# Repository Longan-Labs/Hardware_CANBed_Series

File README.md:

Eagle file sor [CANBed Series](https://www.longan-labs.cc/can-bus/canbed.html)

Include:

* [CANBed V1](https://www.longan-labs.cc/1030008.html)
* [CANBed FD](https://www.longan-labs.cc/1030009.html)
* [CANBed M0](https://www.longan-labs.cc/1030014.html)
* [CANBed M4](https://www.longan-labs.cc/1030013.html)

Click on [Longan-Labs.cc](https://www.longan-labs.cc/) to get the product you need.

Contact [support@longan-labs.cc](support@longan-labs.cc) if you need help.

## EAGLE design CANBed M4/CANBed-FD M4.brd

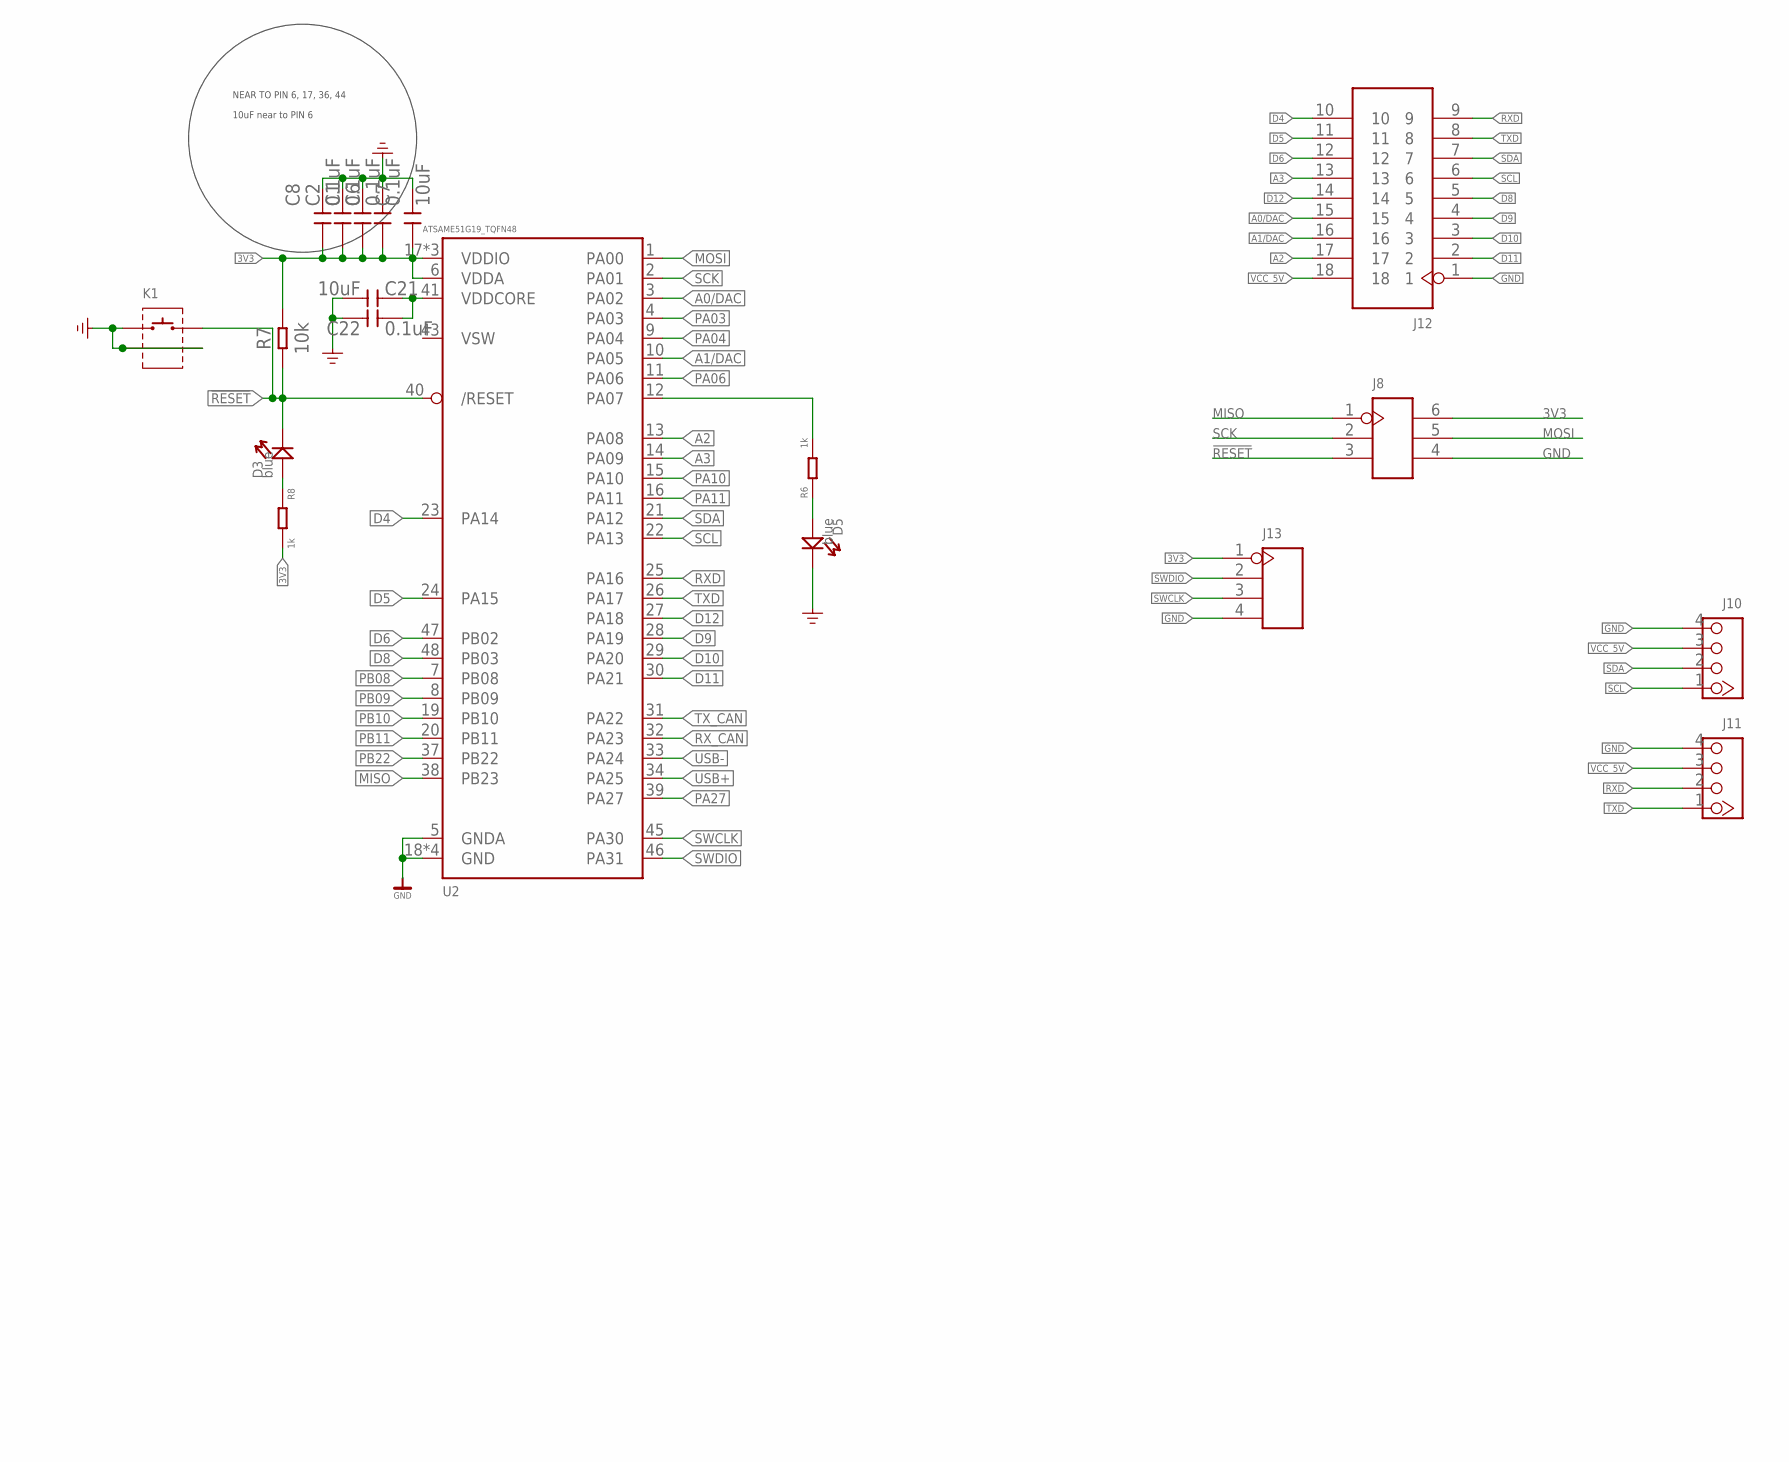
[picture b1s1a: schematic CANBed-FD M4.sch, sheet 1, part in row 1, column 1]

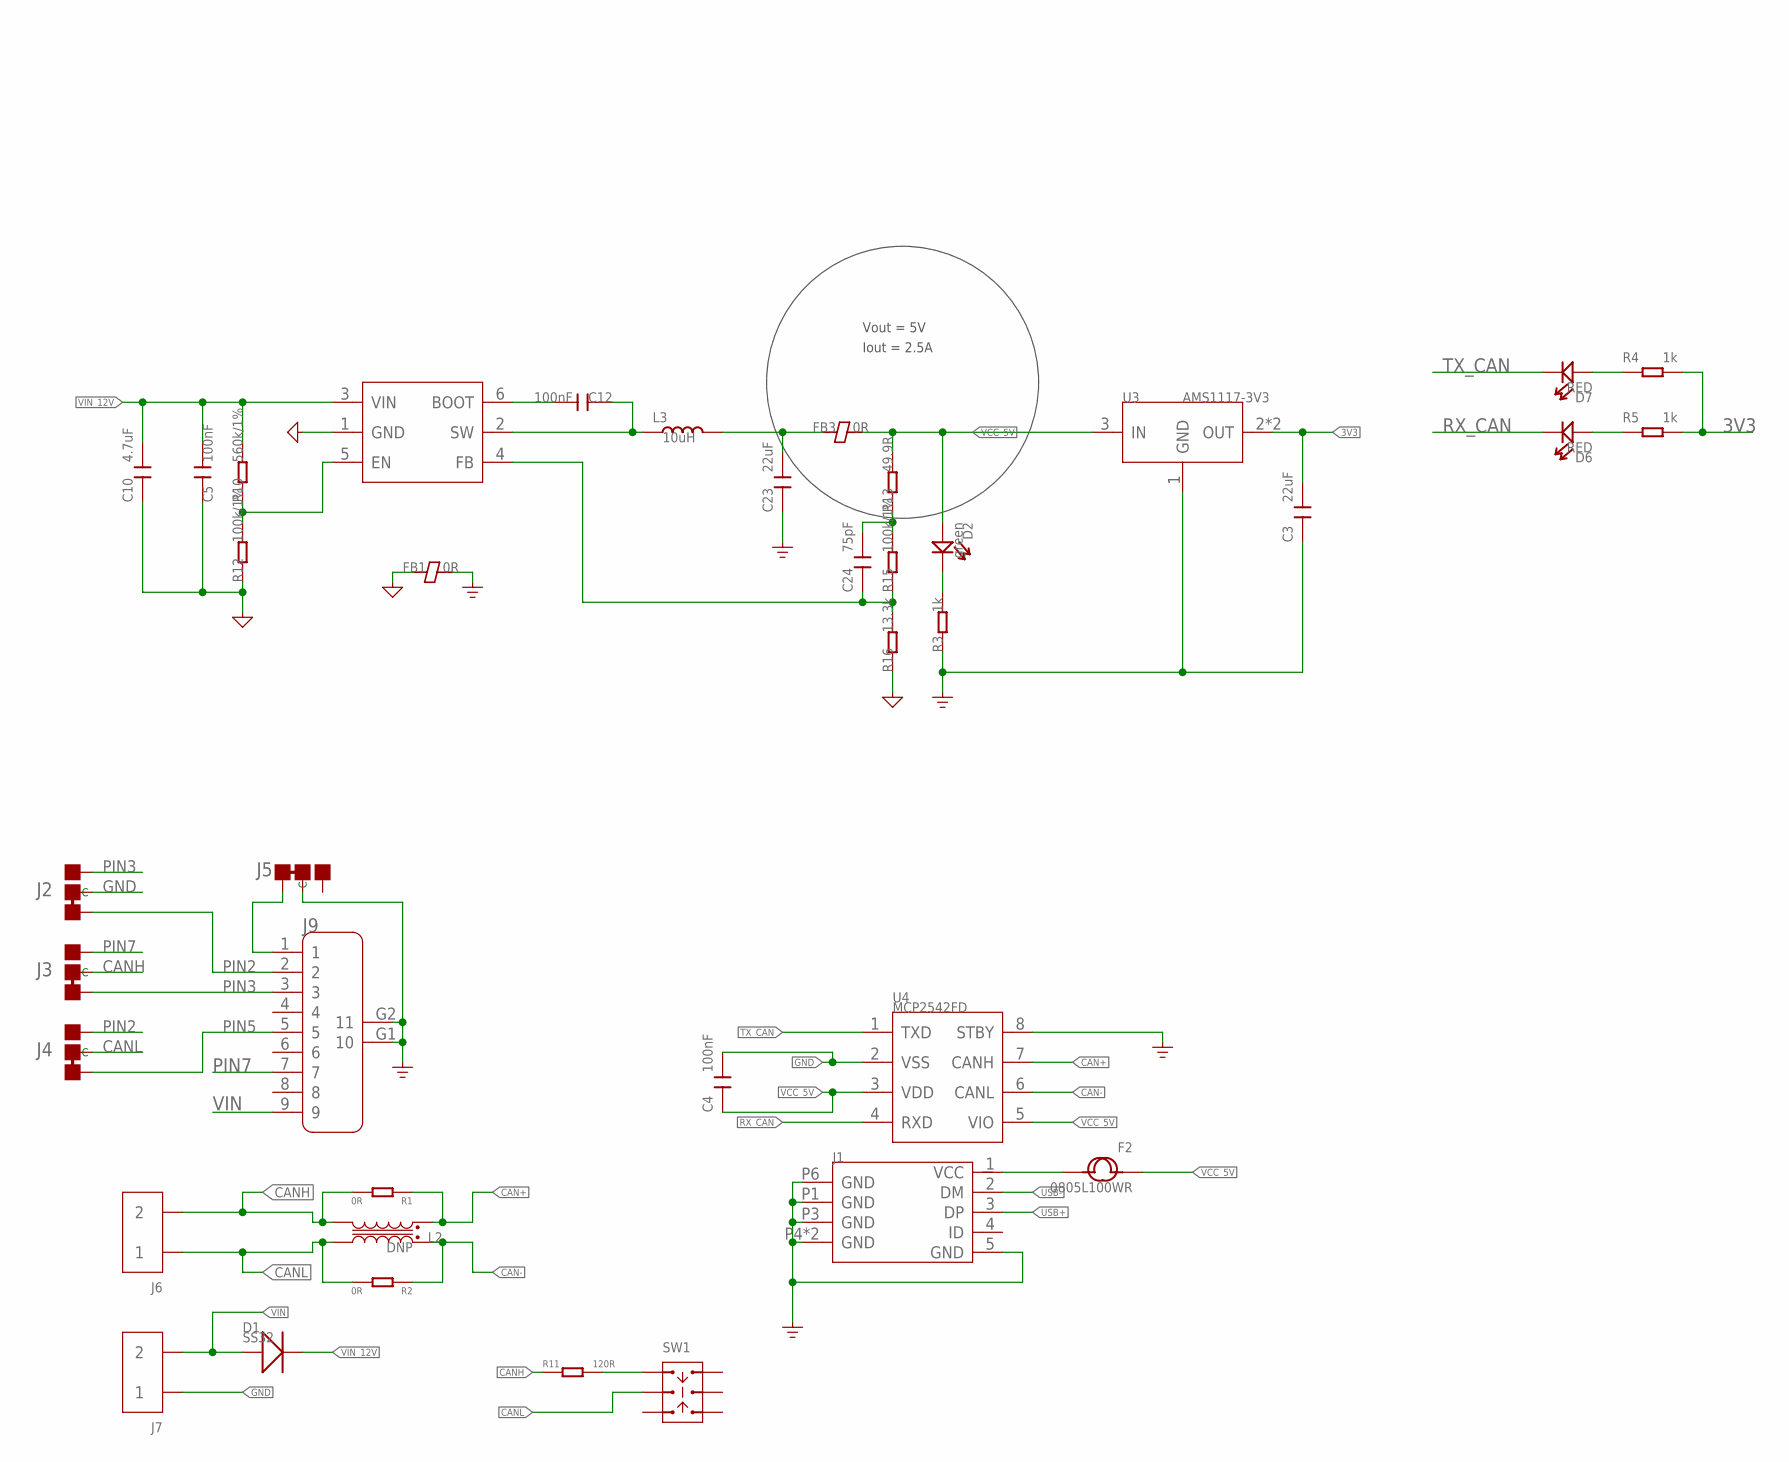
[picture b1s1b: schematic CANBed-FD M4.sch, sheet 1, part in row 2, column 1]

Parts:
C1, C2, C6, C8, C21: 0.1uF; C0603
C3, C23: 22uF; C1206
C4, C5, C12: 100nF; C0603
C7, C22: 10uF; C0603
C10: 4.7uF; C1206
C24: 75pF; C0603
D1: SS32; DO-214AC
D2: green; LED-0603
D3, D5: blue; LED-0603
D6, D7: RED; LED-0603
F2: 0805L100WR; F0805
FB1, FB3: 0R; F0805
J1: MICRO-USB5+4P-320010050; MICRO-USB5+5P-SMD-0.65-7.2X5.06MM
J2, J3, J4, J5: JUMPER-3P-SHORT; 3P-SMD-SHORT
J6, J7: SCREW-TERMINAL-2P'5.08'; H2-5.0-10.5X8.0MM
J8: HEADER-2X3P-2.54; H2X3-2.54
J9: DB9'MEAL'; DB9-MEAL
J10, J11: 320110033; HW4-2.0
J12: HEADER-2X9P-2.54; H2X9-2.54
J13: HEADER-4P-65/35MIL; H4-2.54
K1: BUTTON-2+2P; SW2+2P-7.7X2.75X3.95MM
L2: DNP; INT4-0.85-2X1.25X1.2MM
L3: 10uH; INT2-SMD-6.6X7.1X3MM
R1, R2: 0R; R0603
R3, R4, R5, R6, R8: 1k; R0603
R7: 10k; R0603
R10: 560k/1%; R0603
R11: 120R; R0603
R12, R15: 100k/1%; R0603
R13: 49.9R; R0603
R16: 13.3k; R0603
SW1: SWITCH-2CH-6P-311010004; SW6-2.54-9.0X3.5X3.2+2.0MM
U1: PMIC-TPS54302; SOT-23-6
U2: ATSAME51G19_TQFN48; TQFN48_7MM; MPN ATSAME51G19A-MF
U3: AMS1117-3V3; SOT-223
U4: MCP2542FD; SOIC8-1.27-5X4MM

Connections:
3V3: C1.1, C2.1, C3.2, C6.1, C7.1, C8.1, J8.6, J13.1, R4.2, R5.2, R7.2, R8.2, U2.6 (VDDA), U2.17 (VDDIO), U2.36 (VDDIO), U2.44 (VDDIO), U3.2 (OUT), U3.TER (OUT)
!RESET: D3.-, J8.3, K1.2, R7.1, U2.40 (/RESET)
A0/DAC: J12.15, U2.3 (PA02)
A1/DAC: J12.16, U2.10 (PA05)
A2: J12.17, U2.13 (PA08)
A3: J12.13, U2.14 (PA09)
AGND: C5.1, C10.1, FB1.1, R12.1, R16.1, U1.1 (GND)
CAN+: L2.4, R1.1, U4.7 (CANH)
CAN-: L2.1, R2.1, U4.6 (CANL)
CANH: J3.MM (C), J6.2, L2.3, R1.2, R11.1
CANL: J4.MM (C), J6.1, L2.2, R2.2, SW1.COM1
D4: J12.10, U2.23 (PA14)
D5: J12.11, U2.24 (PA15)
D6: J12.12, U2.47 (PB02)
D8: J12.5, U2.48 (PB03)
D9: J12.4, U2.28 (PA19)
D10: J12.3, U2.29 (PA20)
D11: J12.2, U2.30 (PA21)
D12: J12.14, U2.27 (PA18)
EXT_PWR: F2.2, J1.1 (VCC)
GND: C1.2, C2.2, C3.1, C4.2, C6.2, C7.2, C8.2, C21.1, C22.2, C23.1, D5.-, FB1.2, J1.5 (GND), J1.P1 (GND), J1.P3 (GND), J1.P4 (GND), J1.P5 (GND), J1.P6 (GND), J2.MM (C), J5.MM (C), J7.1, J8.4, J9.G1 (10), J9.G2 (11), J10.4, J11.4, J12.1, J13.4, K1.1, K1.S1, K1.S2, R3.1, U2.5 (GNDA), U2.18 (GND), U2.35 (GND), U2.42 (GND), U2.THERMAL (GND), U3.1 (GND), U4.2 (VSS), U4.8 (STBY)
MISO: J8.1, U2.38 (PB23)
MOSI: J8.5, U2.1 (PA00)
unnamed: D3.+, R8.1
unnamed: D7.+, R4.1
unnamed: D2.-, R3.2
unnamed: R10.1, R12.2, U1.5 (EN)
unnamed: C21.2, C22.1, U2.41 (VDDCORE)
unnamed: R6.2, U2.12 (PA07)
unnamed: D5.+, R6.1
unnamed: C12.1, L3.1, U1.2 (SW)
unnamed: J5.11 (L), J9.1
unnamed: C12.2, U1.6 (BOOT)
unnamed: D6.+, R5.1
unnamed: R11.2, SW1.CH1A
unnamed: C23.2, FB3.1, L3.2
unnamed: C24.2, R13.1, R15.2
unnamed: C24.1, R15.1, R16.2, U1.4 (FB)
PA03: U2.4 (PA03)
PA04: U2.9 (PA04)
PA06: U2.11 (PA06)
PA10: U2.15 (PA10)
PA11: U2.16 (PA11)
PA27: U2.39 (PA27)
PB08: U2.7 (PB08)
PB09: U2.8 (PB09)
PB10: U2.19 (PB10)
PB11: U2.20 (PB11)
PB22: U2.37 (PB22)
PIN2: J2.11 (L), J4.00 (R), J9.2
PIN3: J2.00 (R), J3.11 (L), J9.3
PIN5: J4.11 (L), J9.5
PIN7: J3.00 (R), J9.7
RXD: J11.2, J12.9, U2.25 (PA16)
RX_CAN: D6.-, U2.32 (PA23), U4.4 (RXD)
SCK: J8.2, U2.2 (PA01)
SCL: J10.1, J12.6, U2.22 (PA13)
SDA: J10.2, J12.7, U2.21 (PA12)
SWCLK: J13.3, U2.45 (PA30)
SWDIO: J13.2, U2.46 (PA31)
TXD: J11.1, J12.8, U2.26 (PA17)
TX_CAN: D7.-, U2.31 (PA22), U4.1 (TXD)
USB+: J1.3 (DP), U2.34 (PA25)
USB-: J1.2 (DM), U2.33 (PA24)
VCC_5V: C4.1, D2.+, F2.1, FB3.2, J10.3, J11.3, J12.18, R13.2, U3.3 (IN), U4.3 (VDD), U4.5 (VIO)
VIN: D1.1 (+), J7.2, J9.9
VIN_12V: C5.2, C10.2, D1.2 (-), R10.2, U1.3 (VIN)

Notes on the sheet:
Vout = 5V
Iout = 2.5A
NEAR TO PIN 6, 17, 36, 44
10uF near to PIN 6

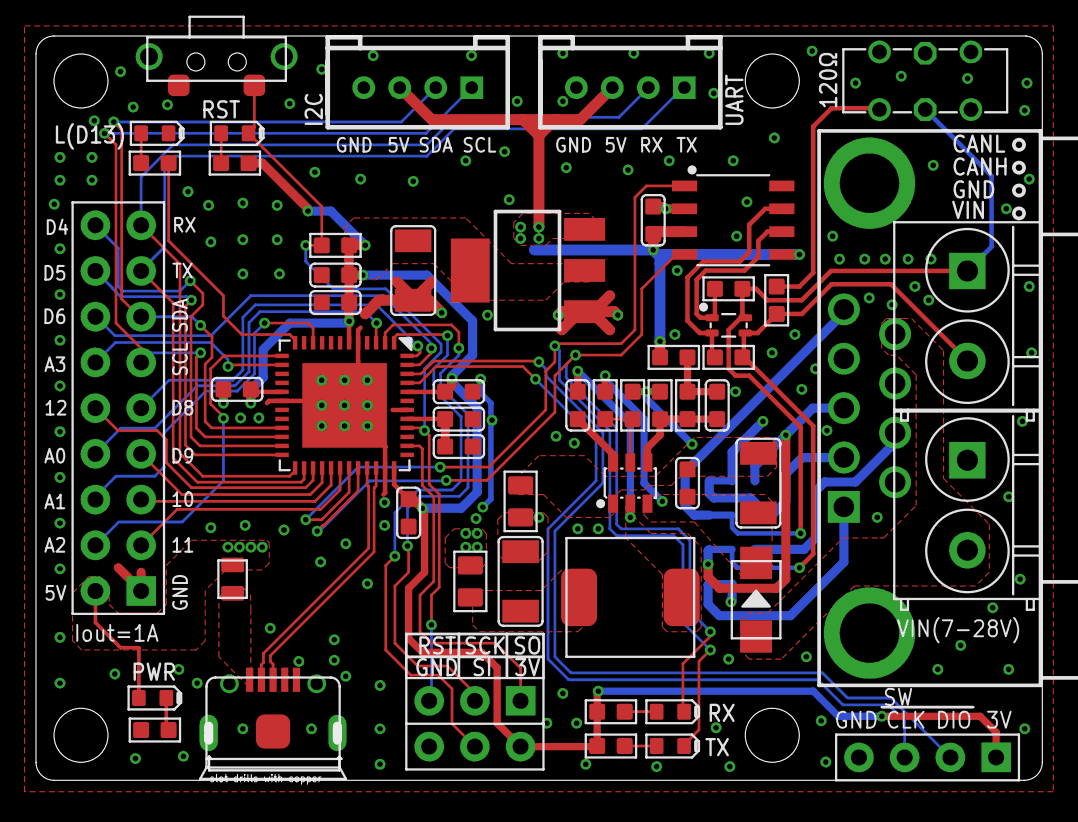
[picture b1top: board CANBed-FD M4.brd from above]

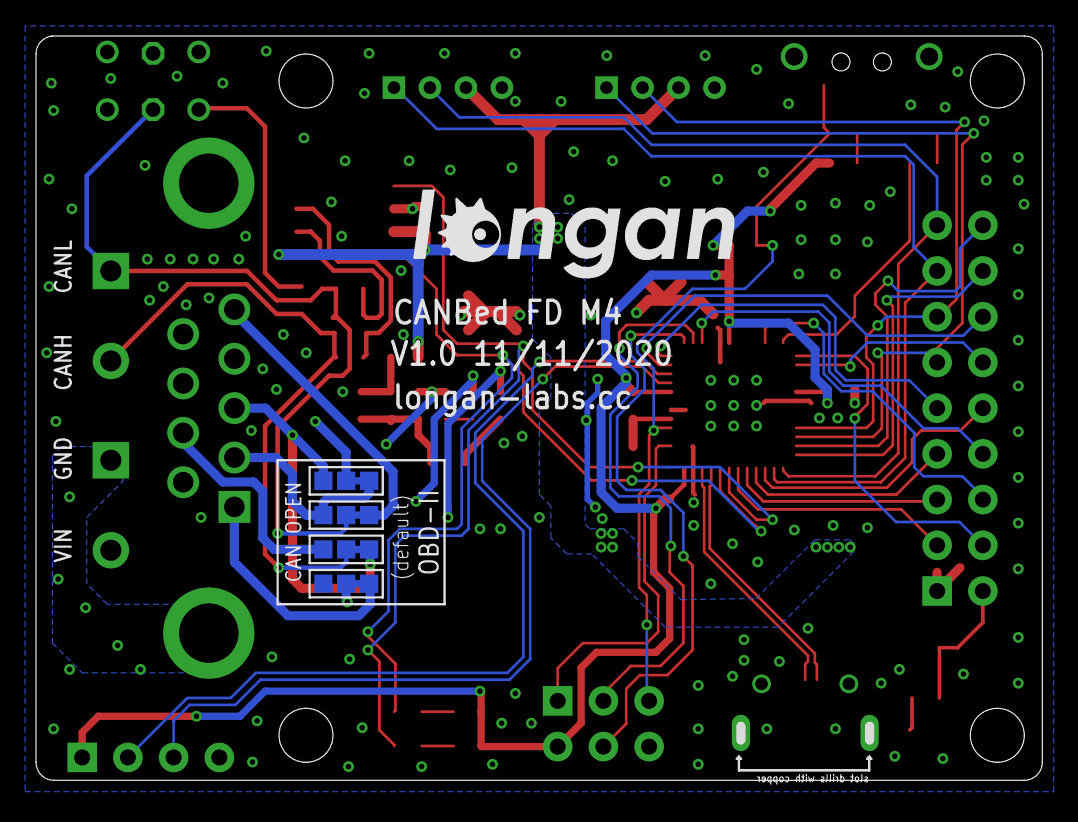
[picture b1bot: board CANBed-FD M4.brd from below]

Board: 2 copper layers, 55.4 x 41.2 mm, 59 parts (5 on the bottom side), 56 nets.

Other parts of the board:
U$12: LONGAN-SILK-SMALL

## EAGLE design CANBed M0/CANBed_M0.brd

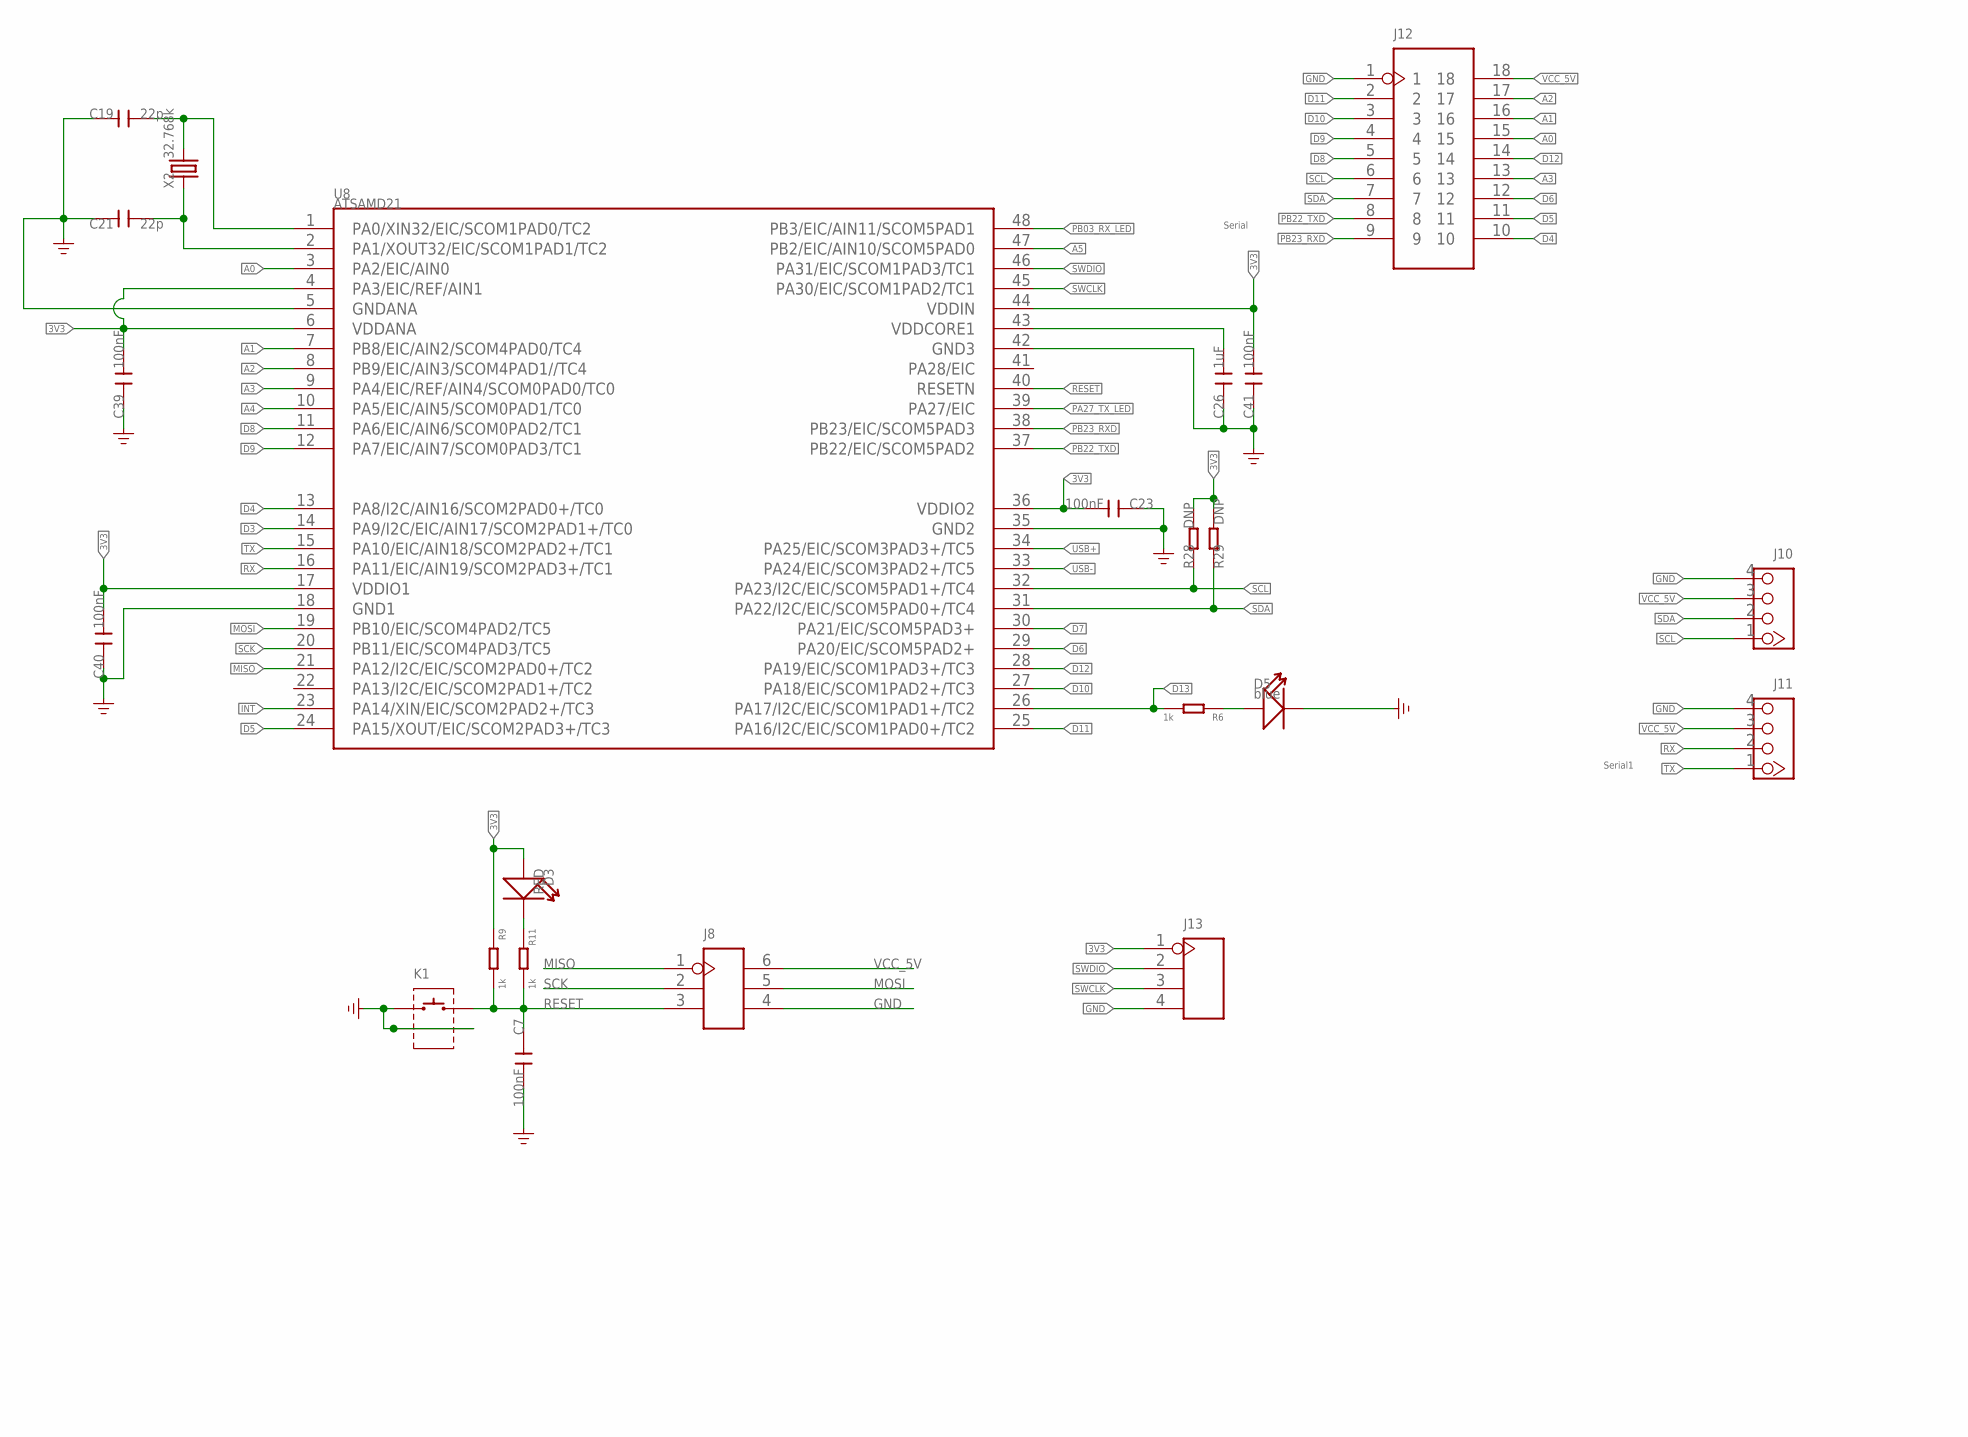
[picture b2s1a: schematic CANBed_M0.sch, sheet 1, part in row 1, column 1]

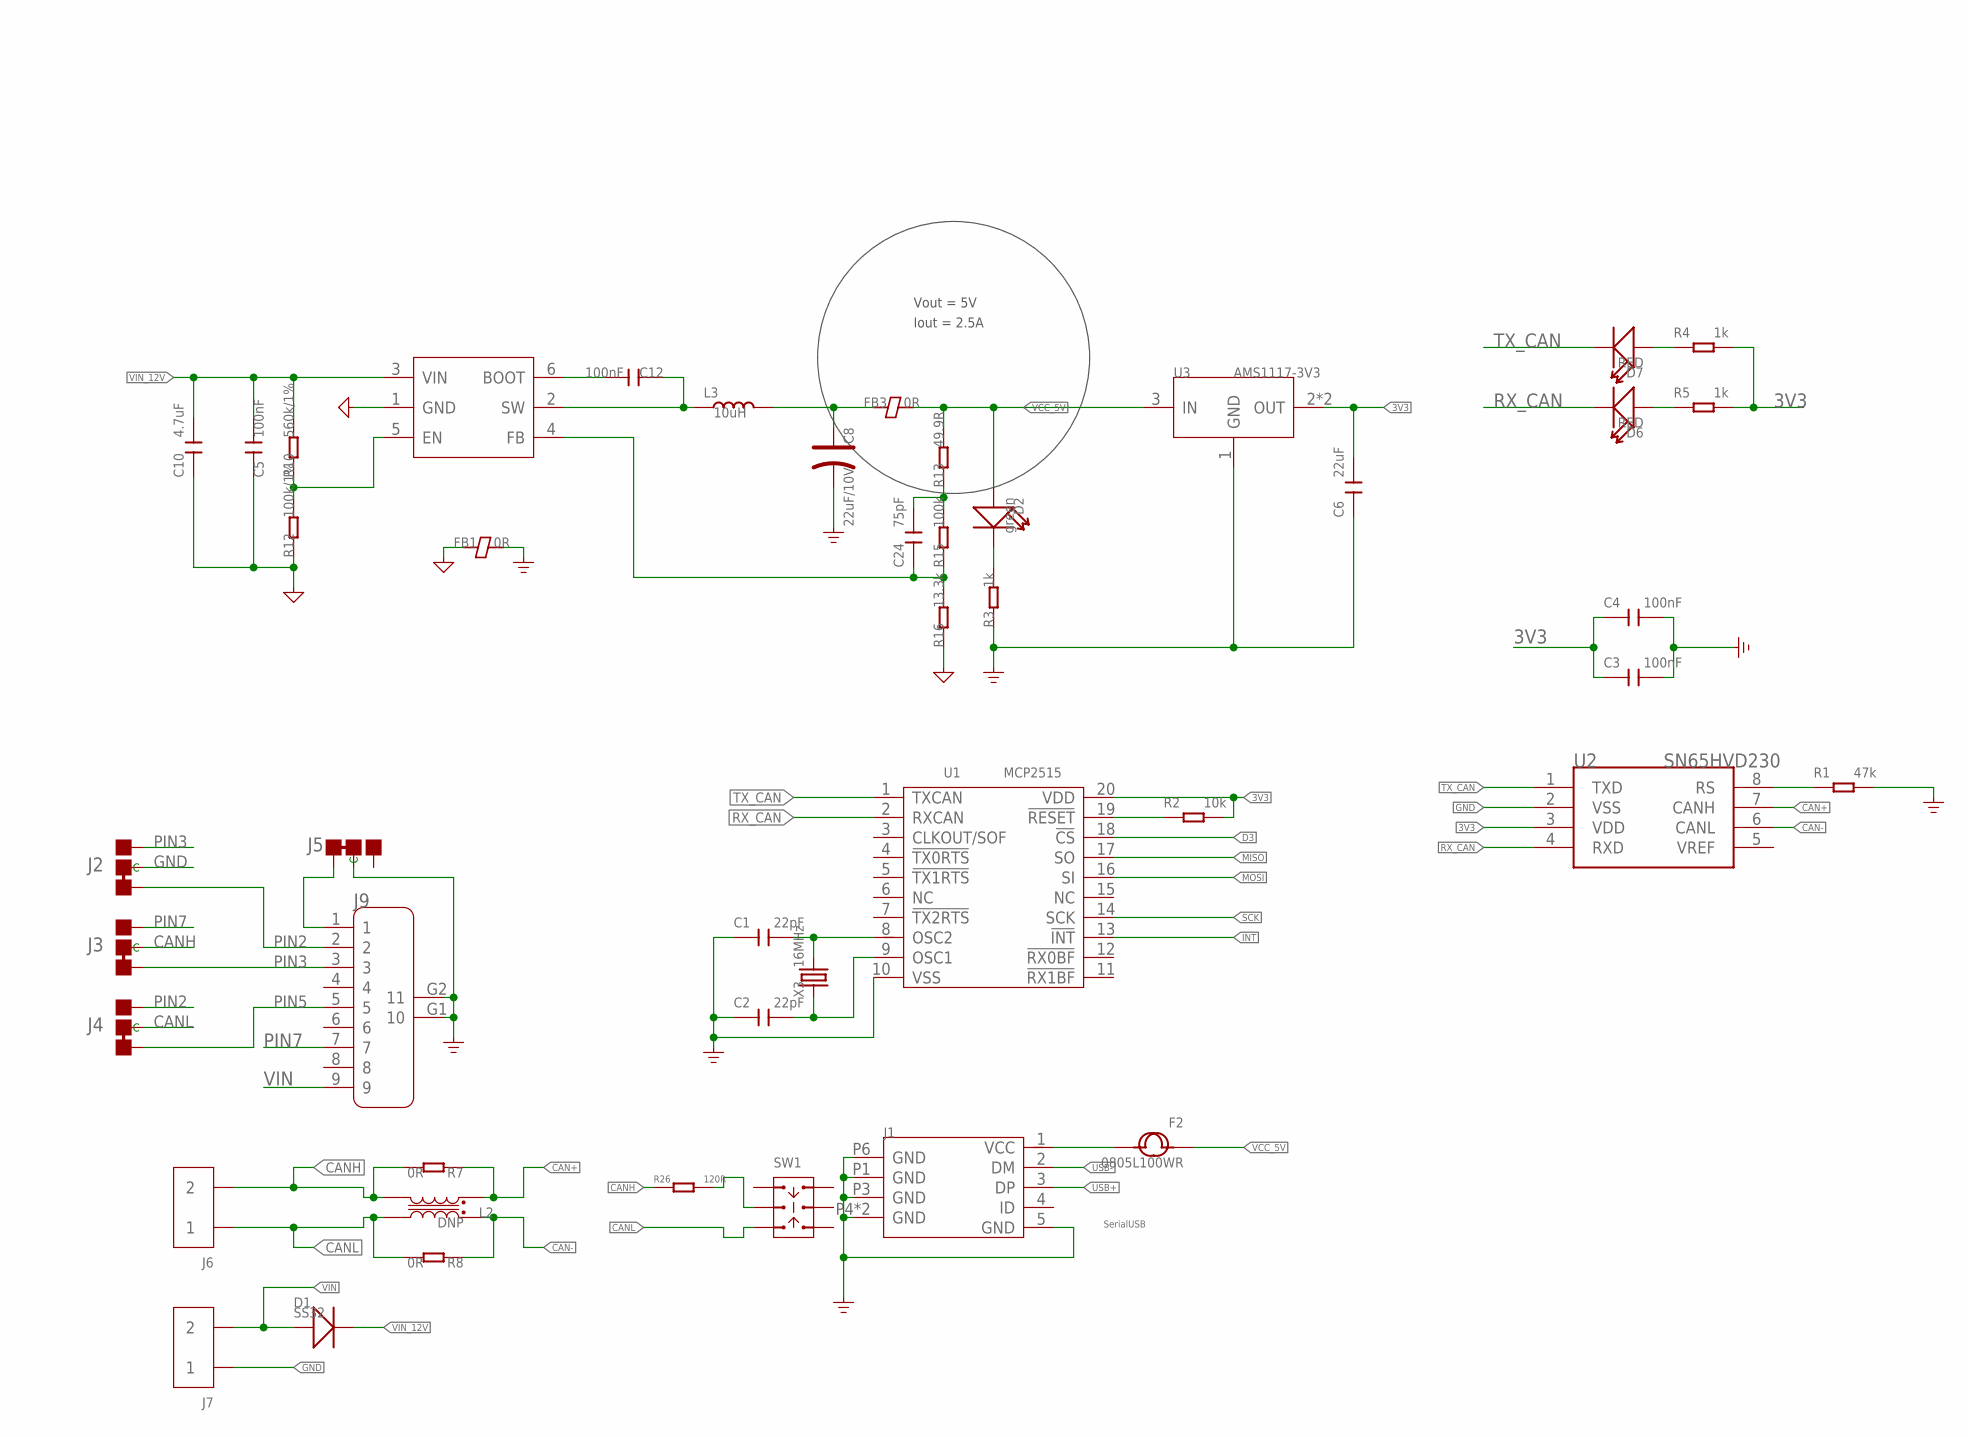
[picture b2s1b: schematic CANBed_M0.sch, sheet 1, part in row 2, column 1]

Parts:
C1, C2: 22pF; C0603
C3, C4, C5, C7, C12, C23, C39, C40, C41: 100nF; C0603
C6: 22uF; C1206
C8: 22uF/10V; AVX-B
C10: 4.7uF; C1206
C19, C21: 22p; C0603
C24: 75pF; C0603
C26: 1uF; C0603
D1: SS32; DO-214AC
D2: green; LED-0603
D3, D6, D7: RED; LED-0603
D5: blue; LED-0603
F2: 0805L100WR; F0805
FB1, FB3: 0R; F0805
J1: MICRO-USB5+4P-320010050; MICRO-USB5+5P-SMD-0.65-7.2X5.06MM
J2, J3, J4, J5: JUMPER-3P-SHORT; 3P-SMD-SHORT
J6, J7: SCREW-TERMINAL-2P'5.08'; H2-5.0-10.5X8.0MM
J8: HEADER-2X3P-2.54; H2X3-2.54
J9: DB9'MEAL'; DB9-MEAL
J10, J11: 320110033; HW4-2.0
J12: HEADER-2X9P-2.54; H2X9-2.54
J13: HEADER-4P-65/35MIL; H4-2.54
K1: BUTTON-2+2P; SW2+2P-7.7X2.75X3.95MM
L2: DNP; INT4-0.85-2X1.25X1.2MM
L3: 10uH; INT2-SMD-6.6X7.1X3MM
R1: 47k; R0603
R2: 10k; R0603
R3, R4, R5, R6, R9, R11: 1k; R0603
R7, R8: 0R; R0603
R10: 560k/1%; R0603
R12: 100k/1%; R0603
R13: 49.9R; R0603
R15: 100k; R0603
R16: 13.3k; R0603
R26: 120R; R0603
R28, R29: DNP; R0603
SW1: SWITCH-2CH-6P-311010004; SW6-2.54-9.0X3.5X3.2+2.0MM
U1: MCP2515; TSSOP20-0.65-6.5X4.4MM
U2: SN65HVD230; SOIC8-6.0
U3: AMS1117-3V3; SOT-223
U6: PMIC-TPS54302; SOT-23-6
U8: ATSAMD21; TQFP48-0.5-7X7MM
X2: 32.768k; X2-SMD-3.2X1.5X0.55MM
X3: 16MHz; X4-SMD-3.2X2.5X0.7MM

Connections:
3V3: C3.1, C4.1, C6.2, C23.2, C39.2, C40.2, C41.2, D3.+, J13.1, R2.2, R4.2, R5.2, R9.1, R28.2, R29.1, U1.20 (VDD), U2.3 (VDD), U3.2 (OUT), U3.TER (OUT), U8.4 (PA3/EIC/REF/AIN1), U8.6 (VDDANA), U8.17 (VDDIO1), U8.36 (VDDIO2), U8.44 (VDDIN)
A0: J12.15, U8.3 (PA2/EIC/AIN0)
A1: J12.16, U8.7 (PB8/EIC/AIN2/SCOM4PAD0/TC4)
A2: J12.17, U8.8 (PB9/EIC/AIN3/SCOM4PAD1//TC4)
A3: J12.13, U8.9 (PA4/EIC/REF/AIN4/SCOM0PAD0/TC0)
A4: U8.10 (PA5/EIC/AIN5/SCOM0PAD1/TC0)
A5: U8.47 (PB2/EIC/AIN10/SCOM5PAD0)
AGND: C5.1, C10.1, FB1.1, R12.1, R16.1, U6.1 (GND)
CAN+: L2.4, R7.1, U2.7 (CANH)
CAN-: L2.1, R8.1, U2.6 (CANL)
CANH: J3.MM (C), J6.2, L2.3, R7.2, R26.1
CANL: J4.MM (C), J6.1, L2.2, R8.2, SW1.CH1B
D3: U1.18 (!CS), U8.14 (PA9/I2C/EIC/AIN17/SCOM2PAD1+/TC0)
D4: J12.10, U8.13 (PA8/I2C/AIN16/SCOM2PAD0+/TC0)
D5: J12.11, U8.24 (PA15/XOUT/EIC/SCOM2PAD3+/TC3)
D6: J12.12, U8.29 (PA20/EIC/SCOM5PAD2+)
D7: U8.30 (PA21/EIC/SCOM5PAD3+)
D8: J12.5, U8.11 (PA6/EIC/AIN6/SCOM0PAD2/TC1)
D9: J12.4, U8.12 (PA7/EIC/AIN7/SCOM0PAD3/TC1)
D10: J12.3, U8.27 (PA18/EIC/SCOM1PAD2+/TC3)
D11: J12.2, U8.25 (PA16/I2C/EIC/SCOM1PAD0+/TC2)
D12: J12.14, U8.28 (PA19/EIC/SCOM1PAD3+/TC3)
D13: R6.2, U8.26 (PA17/I2C/EIC/SCOM1PAD1+/TC2)
EXT_PWR: F2.2, J1.1 (VCC)
GND: C1.1, C2.1, C3.2, C4.2, C6.1, C7.2, C8.-, C19.2, C21.2, C23.1, C26.1, C39.1, C40.1, C41.1, D5.-, FB1.2, J1.5 (GND), J1.P1 (GND), J1.P3 (GND), J1.P4 (GND), J1.P5 (GND), J1.P6 (GND), J2.MM (C), J5.MM (C), J7.1, J8.4, J9.G1 (10), J9.G2 (11), J10.4, J11.4, J12.1, J13.4, K1.1, K1.S1, K1.S2, R1.2, R3.1, U1.10 (VSS), U2.2 (VSS), U3.1 (GND), U8.5 (GNDANA), U8.18 (GND1), U8.35 (GND2), U8.42 (GND3)
INT: U1.13 (!INT), U8.23 (PA14/XIN/EIC/SCOM2PAD2+/TC3)
MISO: J8.1, U1.17 (SO), U8.21 (PA12/I2C/EIC/SCOM2PAD0+/TC2)
MOSI: J8.5, U1.16 (SI), U8.19 (PB10/EIC/SCOM4PAD2/TC5)
unnamed: D2.-, R3.2
unnamed: D7.+, R4.1
unnamed: R10.1, R12.2, U6.5 (EN)
unnamed: R26.2, SW1.COM1
unnamed: D3.-, R11.1
unnamed: D5.+, R6.1
unnamed: C12.1, L3.1, U6.2 (SW)
unnamed: J5.11 (L), J9.1
unnamed: C12.2, U6.6 (BOOT)
unnamed: D6.+, R5.1
unnamed: C1.2, U1.8 (OSC2), X3.3 (2)
unnamed: C2.2, U1.9 (OSC1), X3.1
unnamed: C8.+, FB3.1, L3.2
unnamed: R1.1, U2.8 (RS)
unnamed: C24.2, R13.1, R15.2
unnamed: C24.1, R15.1, R16.2, U6.4 (FB)
unnamed: C19.1, U8.1 (PA0/XIN32/EIC/SCOM1PAD0/TC2), X2.2
unnamed: C21.1, U8.2 (PA1/XOUT32/EIC/SCOM1PAD1/TC2), X2.1
unnamed: C26.2, U8.43 (VDDCORE1)
PA27_TX_LED: U8.39 (PA27/EIC)
PB03_RX_LED: U8.48 (PB3/EIC/AIN11/SCOM5PAD1)
PB22_TXD: J12.8, U8.37 (PB22/EIC/SCOM5PAD2)
PB23_RXD: J12.9, U8.38 (PB23/EIC/SCOM5PAD3)
PIN2: J2.11 (L), J4.00 (R), J9.2
PIN3: J2.00 (R), J3.11 (L), J9.3
PIN5: J4.11 (L), J9.5
PIN7: J3.00 (R), J9.7
RESET: C7.1, J8.3, K1.2, R9.2, R11.2, U8.40 (RESETN)
RST_N: R2.1, U1.19 (!RESET)
RX: J11.2, U8.16 (PA11/EIC/AIN19/SCOM2PAD3+/TC1)
RX_CAN: D6.-, U1.2 (RXCAN), U2.4 (RXD)
SCK: J8.2, U1.14 (SCK), U8.20 (PB11/EIC/SCOM4PAD3/TC5)
SCL: J10.1, J12.6, R28.1, U8.32 (PA23/I2C/EIC/SCOM5PAD1+/TC4)
SDA: J10.2, J12.7, R29.2, U8.31 (PA22/I2C/EIC/SCOM5PAD0+/TC4)
SWCLK: J13.3, U8.45 (PA30/EIC/SCOM1PAD2/TC1)
SWDIO: J13.2, U8.46 (PA31/EIC/SCOM1PAD3/TC1)
TX: J11.1, U8.15 (PA10/EIC/AIN18/SCOM2PAD2+/TC1)
TX_CAN: D7.-, U1.1 (TXCAN), U2.1 (TXD)
USB+: J1.3 (DP), U8.34 (PA25/EIC/SCOM3PAD3+/TC5)
USB-: J1.2 (DM), U8.33 (PA24/EIC/SCOM3PAD2+/TC5)
VCC_5V: D2.+, F2.1, FB3.2, J8.6, J10.3, J11.3, J12.18, R13.2, U3.3 (IN)
VIN: D1.1 (+), J7.2, J9.9
VIN_12V: C5.2, C10.2, D1.2 (-), R10.2, U6.3 (VIN)

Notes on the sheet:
Vout = 5V
Iout = 2.5A
Serial
Serial1
SerialUSB

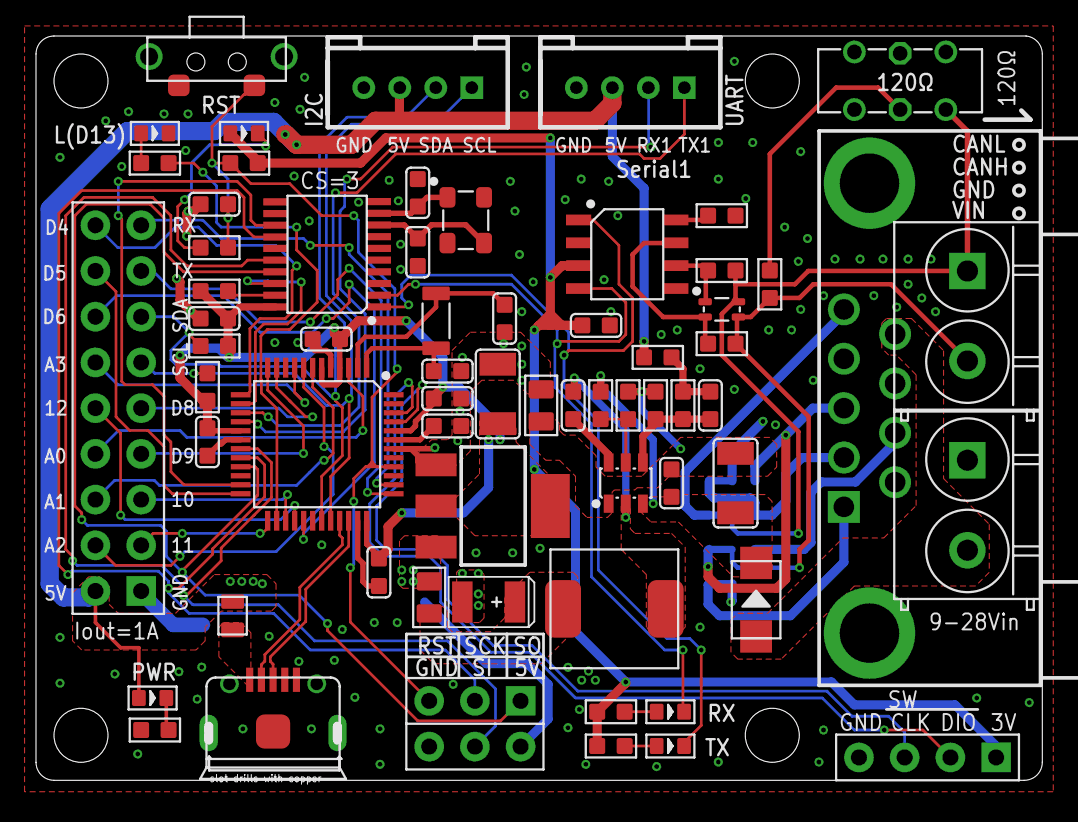
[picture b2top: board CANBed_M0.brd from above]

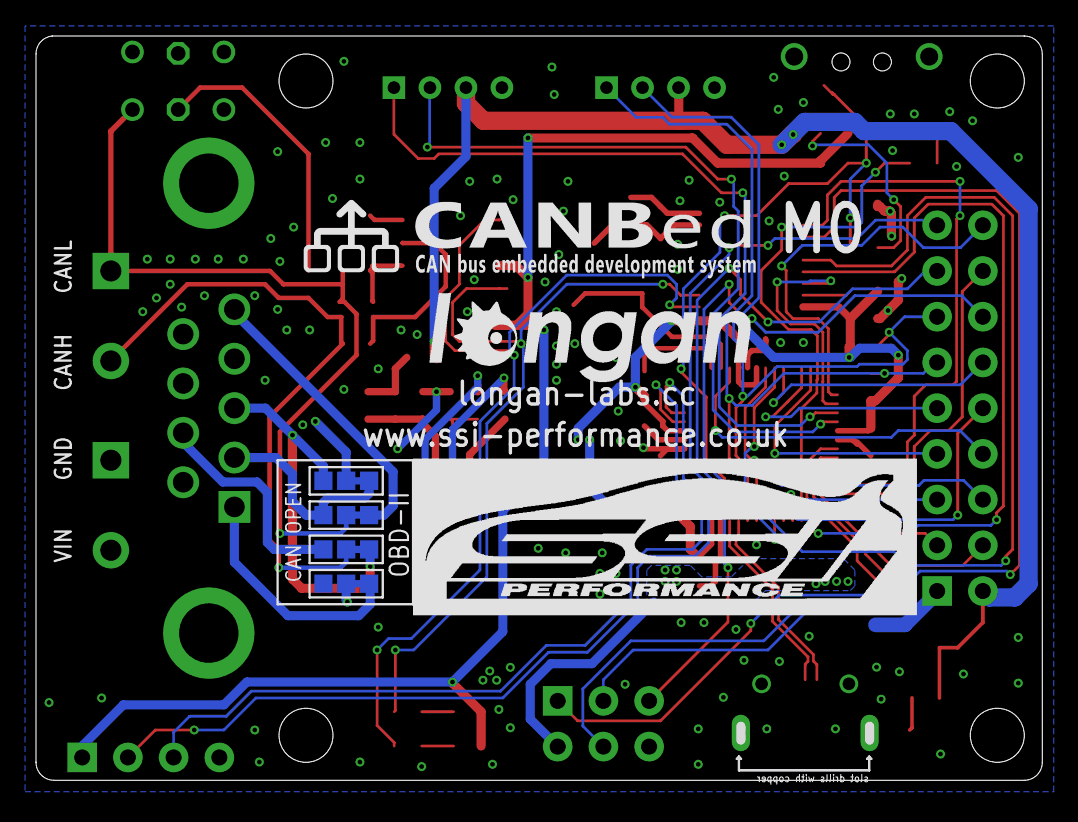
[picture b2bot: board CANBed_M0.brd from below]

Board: 2 copper layers, 55.4 x 41.2 mm, 70 parts (5 on the bottom side), 66 nets.

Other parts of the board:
U$12: LONGAN-SILK-SMALL

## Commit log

2021-01-03 add fukes
2021-08-08 update canbed fd
